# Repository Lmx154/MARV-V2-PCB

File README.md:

# MARV V2 flight controller

A small RP2354B flight controller for rockets and drones: a 6-axis IMU, a high-g
accelerometer and a barometer on their own buses, native four-bit microSD
logging, USB-C, and an IO block for GPS, ELRS, a magnetometer and servos. Power
conversion uses a purchased module that plugs onto the board at J17, so the
converter and FC mount as one unit; the FC takes its regulated 5 V (or USB) and
makes its own 3.3 V rails.

**License:** hardware/docs CC0, code 0BSD, no attribution required. Provided
as-is; see [LICENSE.md](LICENSE.md).

Open [MARV-V2.kicad_pro](MARV-V2.kicad_pro) in **KiCad 10**. The repository holds
the schematic and routed board, local footprints and 3D models, a datasheet
source index, the design checks, and the input-power simulation. There
is no firmware here.

**Status, Rev 2 (2026-11-11): schematic and board updated from Rev 1.** The 32.000 kHz oscillator X1
and its capacitor C1 are removed; U20 GPIO27 now drives ICM_CLKIN to the ICM-45686 CLKIN pin
(firmware generates the 32.000 kHz clock), and U24 is populated with the APS6404L-3SQN-SN 8 MB QSPI
PSRAM. Source DRC: 235 violations (22 accepted errors, 213 warnings), 0 unconnected, 0 schematic-parity
issues; the accepted errors are the same set as Rev 1. ERC: 0 violations. The manufacturing panel and
the `production/` package were regenerated for Rev 2 on 2026-11-11.

**Status, Rev 1 (2026-10-27): routed; manufacturing frame and `production/` package regenerated
from this revision.** Source DRC: 206 violations (22 accepted errors, 184 warnings), 0 unconnected,
0 schematic-parity issues. The accepted errors are 18 GND-via hole clearances in the RP2350 (U20)
exposed pad (JLC hole-in-pad rule), 3 USB pair clearances at the connector and MCU pins, and 1 SW1/J10
courtyard overlap. ERC: 0 violations. The [72 × 72 mm manufacturing frame](reports/manufacturing-panel.md)
supplies rails/fiducials for Standard assembly. Review JLCPCB previews before ordering.

**Converter and ESC pads:** J17 is a 1x03, 2.54 mm converter interface
(1 OUT+, 2 GND, 3 IN+) with no EN contact. J3 is an eight-pad ESC pad row; pad 7 is raw
battery VIN. See [converter review](reports/converter-module-review.md).

[Design specification](DESIGN_SPEC.md) · [GPIO pinout](PINOUT.md) ·
[Libraries](LIBRARIES.md) · [Datasheets](datasheets/README.md) ·
[JLCPCB DFM and routing](reports/jlc-dfm-routing.md) · [Working rules](AGENTS.md)

**See the results without running anything:** the [results website](https://lmx154.github.io/MARV-V2-PCB/)
shows the ngspice power-input waveforms, the netlist and footprint checks, and the
DRC/ERC summary for the current revision. Refresh it with `python3 tools/build_site.py`
(writes `site/`; pushing `site/` to master republishes it via GitHub Pages).

## Repository map

```text
MARV-V2.kicad_pro / _pcb / _sch    project, routed board, root schematic
*.kicad_sch                        11 sub-sheets: power OR / 3V3 / VBAT, MCU, IMU, high-g, baro, SD, USB & debug, IO block, QSPI PSRAM
MARV-V2.kicad_dru, MARV_Sensors.kicad_sym, *-lib-table    custom rules, project symbols, library tables
MARV-V2-panel.kicad_*              one-board manufacturing frame for Standard assembly with customer-supplied rails
fabrication-toolkit-options.json   native Fabrication Toolkit settings for JLCPCB order exports
DESIGN_SPEC.md, PINOUT.md          intended circuit, boundaries and design decisions; every GPIO with its alternates
LIBRARIES.md, AGENTS.md            footprint/model provenance; working rules
MARV_Packages.pretty/, .3dshapes/  local footprints and STEP models
datasheets/                        datasheet source index (PDFs are downloaded locally, not distributed)
tools/                             netlist checker, footprint audit, input-power simulation, PCB renderer, 3d/ (STEP inspection)
tools/panel/                       manufacturing-frame sync and checks; README has the refresh sequence
simulations/                       input-power SPICE deck, README and generated results
reports/                           decision and review records (table below)
orders/rev1/                       Rev 1 JLCPCB order record: exact upload files, all order options, BOM as ordered
orders/rev2/                       Rev 2 JLCPCB order package: upload files and the options to select (same as Rev 1)
images/                            PCB renders used in this README
site/                              results website (simulation, checks), built by tools/build_site.py
.github/workflows/pages.yml        publishes site/ with GitHub Pages
LICENSE.md, LICENSES/              project licence and upstream library notices
production/, build/                generated output; untracked
```

## The board

| Front | Back |
| :---: | :---: |
|  |  |

3D renders of the saved Rev 2 PCB (regenerated 2026-11-11 with the project's own CC0 models for
J4, J11, C19, D20, U20 and the three sensors). J17 is the three-pin header on the front's left edge. Click
either image for the full-resolution view.

To refresh both images after saving PCB changes, run:

```sh
python3 tools/render_pcb.py
```

Requires Python 3 and KiCad 10 with its 3D model libraries. The script renders
high-resolution PNGs into `images/pcb/` without modifying the design. Update the
images after PCB changes to keep this gallery current.

| | |
|---|---|
| MCU | RP2354B (QFN-80, 2 MB in-package flash), 8 MB QSPI PSRAM (U24), 12 MHz crystal, USB-C device port, WS2812C status LED, RESET and BOOTSEL buttons, SWD header |
| Size / stack | 50.7 × 45.5 mm finished outline (72 × 72 mm manufacturing frame), four layers: F.Cu signals · In1 solid GND · In2 V3V3_SYS plane · B.Cu signals. 1.6 mm FR-4, 1 oz outer / 0.5 oz inner, green mask, ENIG |
| Rules | 0.15 mm minimum track and clearance (Signal netclass 0.10 / 0.10 mm), through vias only (0.60 / 0.30 mm; Signal class 0.45 / 0.30 mm), no blind/buried/micro vias — JLCPCB's standard four-layer tier with no paid options |
| Assembly | Front side SMT at JLCPCB (89 placements, 34 unique LCSC parts). Hand-fitted / unpopulated: ESC pad row J3 (back), SWD header J10 (front). J17 converter header is hand-fitted and excluded from the position file |
| Mounting | Four M3 grommet holes (4.0 mm) with GND rings, on a 30.5 × 30.5 mm square pattern. The 5 V converter module mounts on the FC itself at J17 |
| Connectors | J3 ESC pads (current, telemetry, PWM1–4, raw battery VIN, GND), J4 USB-C, J6/J7/J8 IO block (14 rows × signal / power / GND), J10 SWD, J11 locking microSD; J17 1x03 2.54 mm converter mount (1 OUT+ / 5V_IN, 2 GND, 3 IN+ / VBAT) |

## Sensor suite

Every sensor has its own bus; no clock or data net is shared between devices, so
each can be driven at its own rate and no transaction blocks another.

| Ref | Part | What it measures | Bus | Interrupts |
|---|---|---|---|---|
| U21 | InvenSense ICM-45686 | 6-axis IMU (gyro + accel), primary attitude source | hardware **SPI0**, exclusive; 32.000 kHz clock generated by firmware on GPIO27 (ICM_CLKIN) to CLKIN (pin 9) | INT1 only |
| U23 | ST LSM6DSK320X | secondary 6-axis IMU with a ±320 g high-g channel for launch / impact / hard landings | hardware **SPI1**, exclusive | INT1, INT2 |
| U22 | Bosch BMP581 | barometric altitude and temperature | hardware **I2C1**, address 0x46 | INT |
| J11 | Molex 47219-2001 microSD | flight log | PIO + DMA, native **four-bit SD** | — |

The three sensors run from the dedicated V3V3_ANA rail with their chip-select
and I²C pull-ups referenced to it, and all four interrupt lines land on
independent GPIOs. Layout follows the makers' notes: the BMP581 has no copper or
solder mask under its body (Bosch §8.2), and the inertial sensors sit close to
the MCU with short SPI runs. Exact GPIO numbers are in [PINOUT.md](PINOUT.md).

## Power architecture

```text
ESC V (raw battery) → J3.7 / VBAT → J17.3 VIN → converter → J17.1 VOUT
                                      ↓ 5V_IN               USB-C VBUS
                                      Q1 (AO3401A)           D1 (1N5819WS)
                                      └────────── V5_SYS ────┘
                                                    ├─ AP63203 buck → V3V3_SYS  (MCU, microSD, IO block, LDO enable)
                                                    ├─ TPS7A2033 LDO → V3V3_ANA (ICM-45686, LSM6DSK320X, BMP581, ADC_AVDD)
                                                    └─ status LED
RP2354B on-chip switcher: V3V3_SYS → 1.1 V core (laid out per RP2350 datasheet §6.3.8)
Converter VIN / J17.3 (VBAT) → 100k / 10k divider → ADC (parallel sensing branch)
```

Nothing that moves is powered through the FC. Motors, servos and ESCs get only
their signal pins. Raw pack voltage supplies the J17 converter and voltage divider.
The full boundary table is in [DESIGN_SPEC.md](DESIGN_SPEC.md#sources-and-loads).

**External 5 V converter on J17.** The converter is a purchased module that
plugs straight onto the FC through J17, a 1x03 2.54 mm vertical pin header:
pin 1 OUT+ (`5V_IN`), pin 2 GND, pin 3 IN+ (`VBAT`, raw battery from ESC V via
J3.7); the module's EN contact is not connected. Because the converter rides on
the board, the stack mounts as one unit, which keeps mounting simple. Its
output enters upstream of Q1/D1, never directly at V5_SYS. Set and verify the 5 V
output before fitting the module. Its body outline and clearance (including
microSD lid access) are not yet verified: the J17 footprint covers the pins only.
See the [converter review](reports/converter-module-review.md).

Battery current comes from the GOKU G55M ESC's analog C output on J3.1 (R53/C78 →
GPIO41/ADC1); VBAT is sensed by R27/R28/C48 on GPIO42/ADC2. The G55M's output
scale and offset still need calibration. See [G55M sensing](reports/g55m-battery-sensing.md).

## Design decisions

The reasons behind each major choice are recorded in [DESIGN_SPEC.md](DESIGN_SPEC.md#design-decisions).

## Validating the power input with simulation

The one thing the board cannot control is how power arrives, so that is the one
thing simulated. `tools/simulate_power_input.py` builds an ngspice deck from the
**saved schematic** (it checks the Q1/D1/C19 wiring before running) and drives
V5_SYS through seven cases: external 5 V only; USB only; both present; USB
plugged in while external stays; USB unplugged; external unplugged; and an
external-only load step. The pass criterion is explicit: the lowest V5_SYS seen
in any event window must stay above the AP63203's 3.8 V input minimum, or the
script exits 1.

```sh
python3 tools/simulate_power_input.py                       # default 0.5 A at V5_SYS
python3 tools/simulate_power_input.py --load 0.3 --usb-voltage 4.75
python3 tools/simulate_power_input.py --load 0.5 --external-load 1.0
```

Latest result ([simulations/RESULTS.md](simulations/RESULTS.md)): lowest event
voltage **4.269 V** during USB removal, margin 0.47 V over the floor; USB-only
operation settles at 4.32 V through D1. Assumptions are stated, not hidden:
0.05 Ω external source, 0.35 Ω USB source, a 0.5 A combined demand that is a
starting point rather than a measured budget, the vendor AO3401A model and a
hand-fitted 1N5819WS curve. It does **not** simulate the downstream regulators,
USB negotiation, sensor noise, layout parasitics or temperature — see
[simulations/README.md](simulations/README.md) for the boundary. Anything
beyond the OR is validated on hardware, not in SPICE.

## Verifying the design

Requirements: Python 3, KiCad 10 with its standard libraries, ngspice. Ordering exports use the installed Fabrication Toolkit plugin.

```sh
mkdir -p build/checks
kicad-cli sch erc --severity-all --exit-code-violations -o build/checks/erc.rpt MARV-V2.kicad_sch
kicad-cli sch export netlist --format kicadxml -o build/checks/netlist.xml MARV-V2.kicad_sch
python3 tools/check_power_netlist.py build/checks/netlist.xml   # rails, all 48 GPIOs, bus endpoints, pull-ups, absent refs
python3 tools/audit_footprints.py build/checks/netlist.xml     # footprint/model availability and pin coverage
kicad-cli pcb drc --schematic-parity --severity-error --severity-warning --format json -o build/checks/drc.json MARV-V2.kicad_pcb
```

Design rules live in `MARV-V2.kicad_pro` (board setup) and `MARV-V2.kicad_dru`
(JLCPCB custom rules); edit them in KiCad. Netclasses: Signal 0.10 mm / 0.10 mm clearance
(vias 0.45 / 0.30 mm); Default, Rail3V3 and CoreDVDD 0.20 mm; Analog3V3 0.30 mm; Power 0.50 mm
(vias 0.80 / 0.40 mm); USB 0.36 mm / 0.18 mm clearance; other vias 0.60 / 0.30 mm. Teardrops are on all vias
and pads except the LGA sensors U21, U22 and U23.

## Ordering

**Rev 1 was ordered from JLCPCB. The exact upload files and every PCB and PCBA option
selected are archived in [orders/rev1/](orders/rev1/README.md). To reorder Rev 1, follow
that record; it takes precedence over the general steps below.**

**The Rev 2 order package (upload files and the options to select, the same settings as Rev 1) is in
[orders/rev2/](orders/rev2/README.md). Rev 2 has not been ordered yet.**

Use the installed [Fabrication Toolkit](https://github.com/bennymeg/Fabrication-Toolkit)
from KiCad's PCB Editor. Project settings are saved in
[fabrication-toolkit-options.json](fabrication-toolkit-options.json); no custom
Gerber, BOM or placement exporter is needed.

1. Open **MARV-V2-panel.kicad_pro** for the Standard assembly export. This is
   a saved manufacturing copy with customer-supplied rails. After circuit-design
   changes, update the original board, synchronize the manufacturing copy, and
   run the checks before exporting. See the [panel notes](reports/manufacturing-panel.md).
2. Click **Fabrication Toolkit → Generate**. The saved options enable automatic
   component translations and exclude DNP parts. The **User.1 V-cut option is on** for the manufacturing panel. Automatic zone
   refill, alternate outlines and plotting all active layers are **off**. Refill zones
   yourself in KiCad when copper changes require it, before the final DRC.
3. Upload the generated files:

   | JLCPCB step | File |
   | --- | --- |
   | PCB fabrication | `production/MARV-V2-panel.zip` (Gerbers and drills with rails) |
   | Assembly parts | `production/bom.csv` |
   | Assembly placement | `production/positions.csv` |

These three files were regenerated together from the Rev 2 manufacturing panel on
**2026-11-11**. The BOM and placements match the saved Rev 2 board; the Gerbers
include the rails, routed channels, V-score annotations and fiducials;
the NPTH drills include tooling holes and the original USB locating holes. The local
`production/order-manifest.json` records source/output SHA-256 hashes, and
`production/SHA256SUMS` checks the three upload files. See the
[panel verification](reports/manufacturing-panel.md) for validation results
and remaining preview checks. Regenerate after any saved design change.

The initial Rev 1 order was **5 PCBs manufactured, 2 assembled on the top side** and
3 bare. Select **1 design, Delivery Format: Panel by Customer (1 × 1), 4 layers, 1.6 mm, green mask, white silk,
ENIG, standard copper and 0.30 mm minimum via holes**. Use
**Standard assembly** and **Edge Rails/Fiducials → Added by Customer**.
The 72 × 72 mm frame contains one finished PCB and uses two full-height
V-scores through its side connections, with no mouse-bite holes or added rail silk. It can be removed after delivery; check the quote no longer includes
JLC's rail-addition service charge.

The schematic's `LCSC` fields and native BOM/position exclusions define the
assembly selection. J6–J8 and J10 are owner-soldered headers; J3, H1–H4
and the graphic footprints are board features. All are
omitted from assembly exports. This leaves **89 front-side placements using
34 distinct LCSC parts**. The plugin generates one BOM row per component value
and note; `tools/panel/merge_bom.py` merges them to one line per LCSC part (34 LCSC parts plus
the J17 line without an LCSC number). JLC's parts-selection page provides current
stock and pricing.

Automatic translations apply the plugin's package rotation corrections; they
are export corrections, not changes to the PCB layout. Review every placement
in JLC's preview, especially the custom sensor footprints and **L20: orientation
dot toward pad 2 / DVDD**. The Rev 2 2026-11-11 export was checked against the
source board (`tools/panel/check_positions.py`): all 89 placements match in part and position.

`production/` is generated and ignored by Git; use the three plugin files above
together. [tools/panel/README.md](tools/panel/README.md) has the exact refresh sequence.

## Reports

Decision and review records, newest first:

| Report | What it records |
|---|---|
| [converter-module-review.md](reports/converter-module-review.md) | The J17 on-board 5 V converter mount, its three-pin interface, battery compatibility and open fit questions |
| [g55m-battery-sensing.md](reports/g55m-battery-sensing.md) | G55M ESC current and battery sensing connections and limits |
| [manufacturing-panel.md](reports/manufacturing-panel.md) | Customer-supplied V-cut frame, Rev 2 order package and panel verification |
| [usb-differential-routing.md](reports/usb-differential-routing.md) | The 0.36 mm / 0.20 mm gap USB differential-pair preset and the manufacturer guidance behind it |
| [jlc-dfm-routing.md](reports/jlc-dfm-routing.md) | JLC capability sources behind every installed constraint |
| [sd-connector-replacement.md](reports/sd-connector-replacement.md) | The locking microSD socket (J11): choice, pinout and footprint |

Placement and routing are done by hand in KiCad and are never regenerated — see
[AGENTS.md](AGENTS.md).

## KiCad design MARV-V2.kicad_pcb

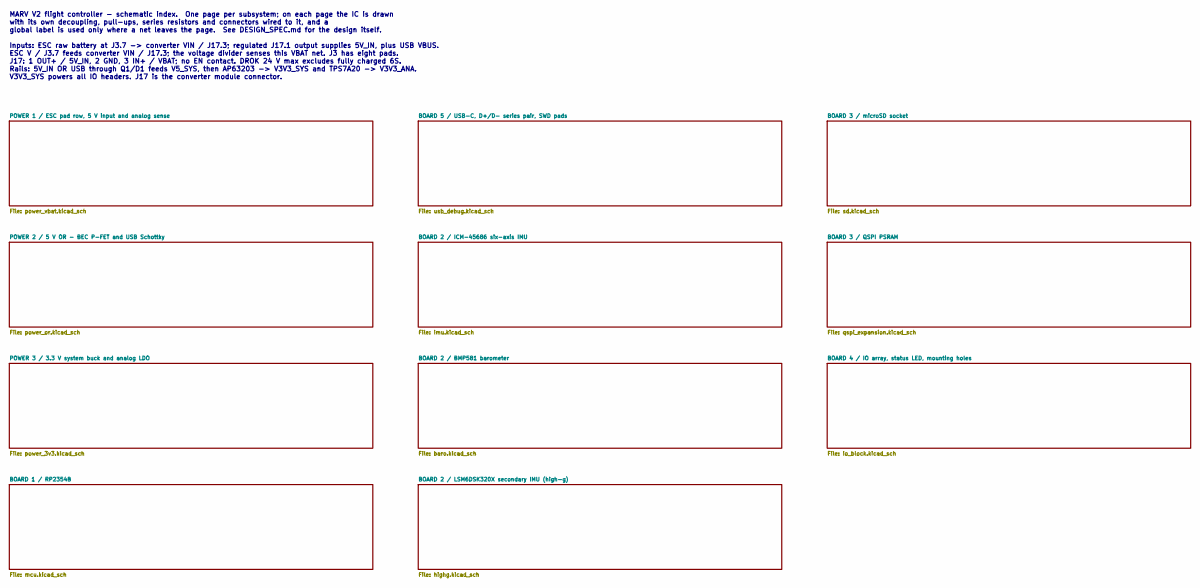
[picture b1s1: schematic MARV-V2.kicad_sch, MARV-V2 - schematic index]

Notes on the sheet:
MARV V2 flight controller - schematic index. One page per subsystem; on each page the IC is drawn with its own decoupling, pull-ups, series resistors and connectors wired to it, and a global label is used only where a net leaves the page. See DESIGN_SPEC.md for the design itself. Inputs: ESC raw ba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

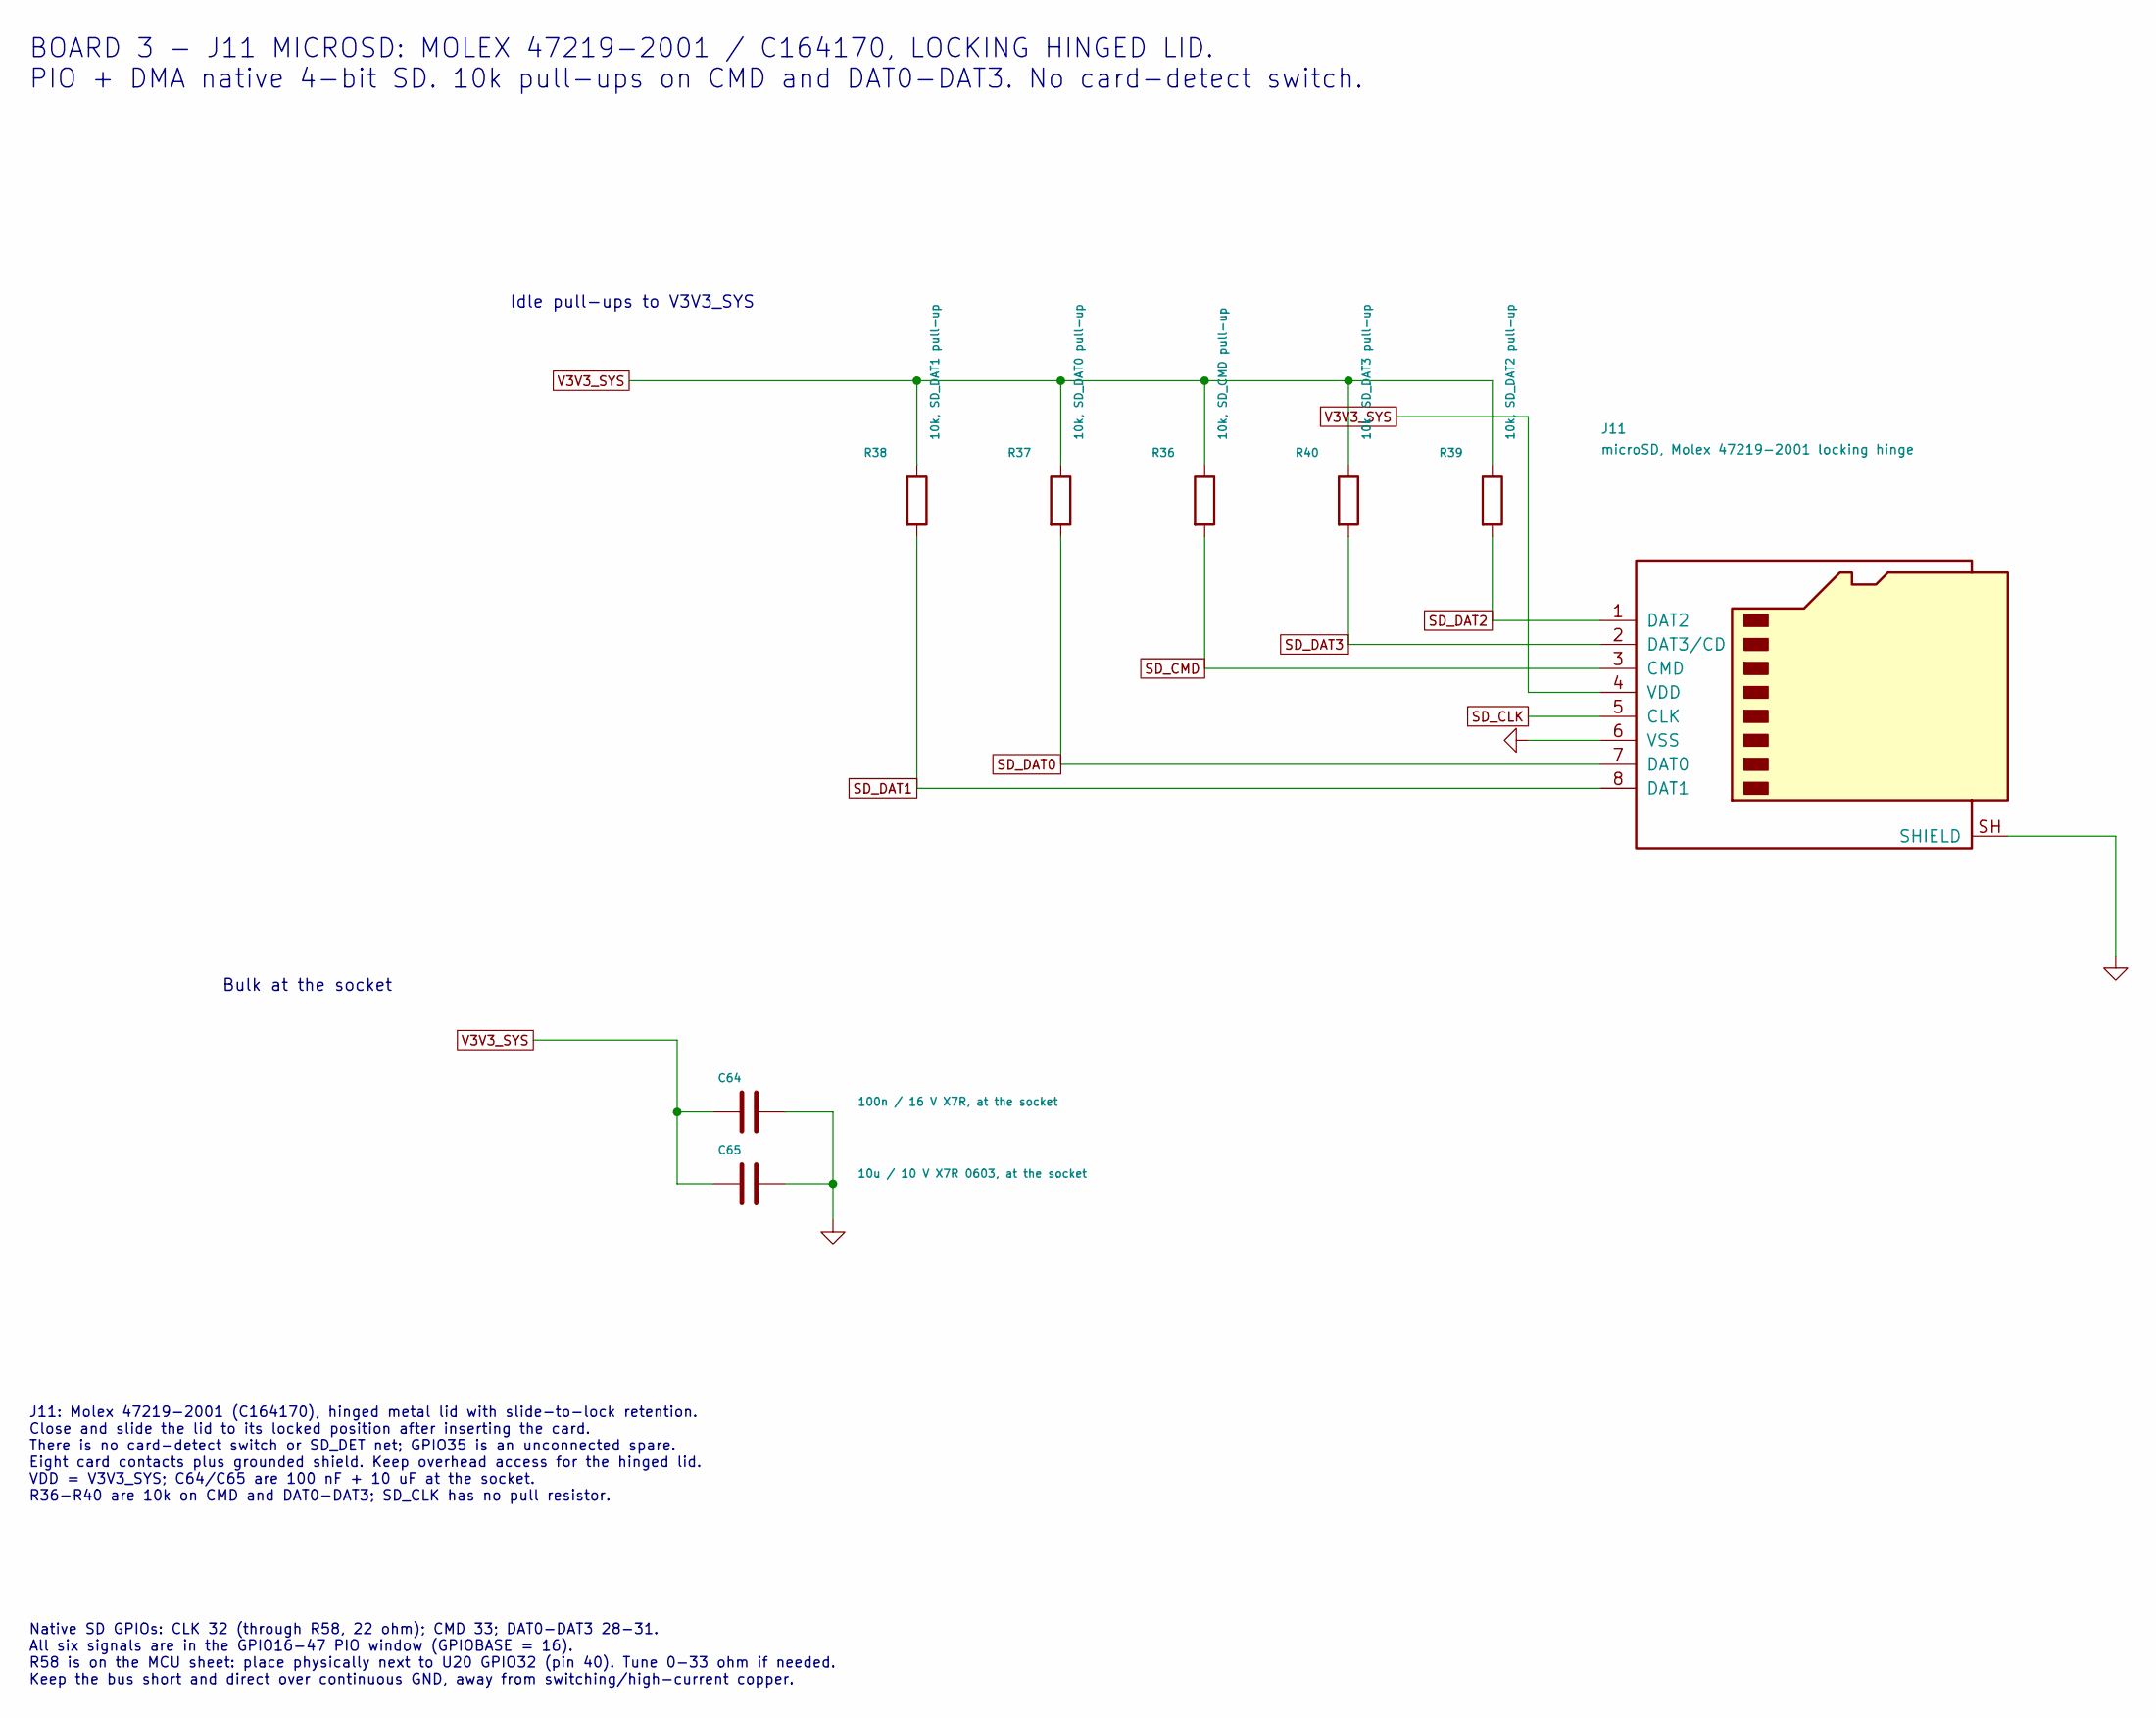
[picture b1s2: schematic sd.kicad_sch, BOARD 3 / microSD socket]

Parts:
C64: 100n / 16 V X7R, at the socket; C_0402_1005Metric; LCSC C1525
C65: 10u / 10 V X7R 0603, at the socket; C_0603_1608Metric; LCSC C96446
J11: microSD, Molex 47219-2001 locking hinge; microSD_HC_Molex_47219-2001; LCSC C164170
R36: 10k, SD_CMD pull-up; R_0402_1005Metric; LCSC C25744
R37: 10k, SD_DAT0 pull-up; R_0402_1005Metric; LCSC C25744
R38: 10k, SD_DAT1 pull-up; R_0402_1005Metric; LCSC C25744
R39: 10k, SD_DAT2 pull-up; R_0402_1005Metric; LCSC C25744
R40: 10k, SD_DAT3 pull-up; R_0402_1005Metric; LCSC C25744

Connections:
GND: C64.2, C65.2, J11.6 (VSS), J11.SH (SHIELD); also elsewhere on the board
SD_CLK: J11.5 (CLK); also elsewhere on the board
SD_CMD: J11.3 (CMD), R36.2; also elsewhere on the board
SD_DAT0: J11.7 (DAT0), R37.2; also elsewhere on the board
SD_DAT1: J11.8 (DAT1), R38.2; also elsewhere on the board
SD_DAT2: J11.1 (DAT2), R39.2; also elsewhere on the board
SD_DAT3: J11.2 (DAT3/CD), R40.2; also elsewhere on the board
V3V3_SYS: C64.1, C65.1, J11.4 (VDD), R36.1, R37.1, R38.1, R39.1, R40.1; also elsewhere on the board

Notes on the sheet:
J11: Molex 47219-2001 (C164170), hinged metal lid with slide-to-lock retention. Close and slide the lid to its locked position after inserting the card. There is no card-detect switch or SD_DET net; GPIO35 is an unconnected spare. Eight card contacts plus grounded shield. Keep overhead access for t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
Idle pull-ups to V3V3_SYS
Native SD GPIOs: CLK 32 (through R58, 22 ohm); CMD 33; DAT0-DAT3 28-31. All six signals are in the GPIO16-47 PIO window (GPIOBASE = 16). R58 is on the MCU sheet: place physically next to U20 GPIO32 (pin 40). Tune 0-33 ohm if needed. Keep the bus short and direct over continuous GND, away from switc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
BOARD 3 - J11 MICROSD: MOLEX 47219-2001 / C164170, LOCKING HINGED LID. PIO + DMA native 4-bit SD. 10k pull-ups on CMD and DAT0-DAT3. No card-detect switch.
Bulk at the socket

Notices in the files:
parts and their libraries:
3D model is the project's own CC0 model built from the DS-000489 package drawing (pp.51-52).
